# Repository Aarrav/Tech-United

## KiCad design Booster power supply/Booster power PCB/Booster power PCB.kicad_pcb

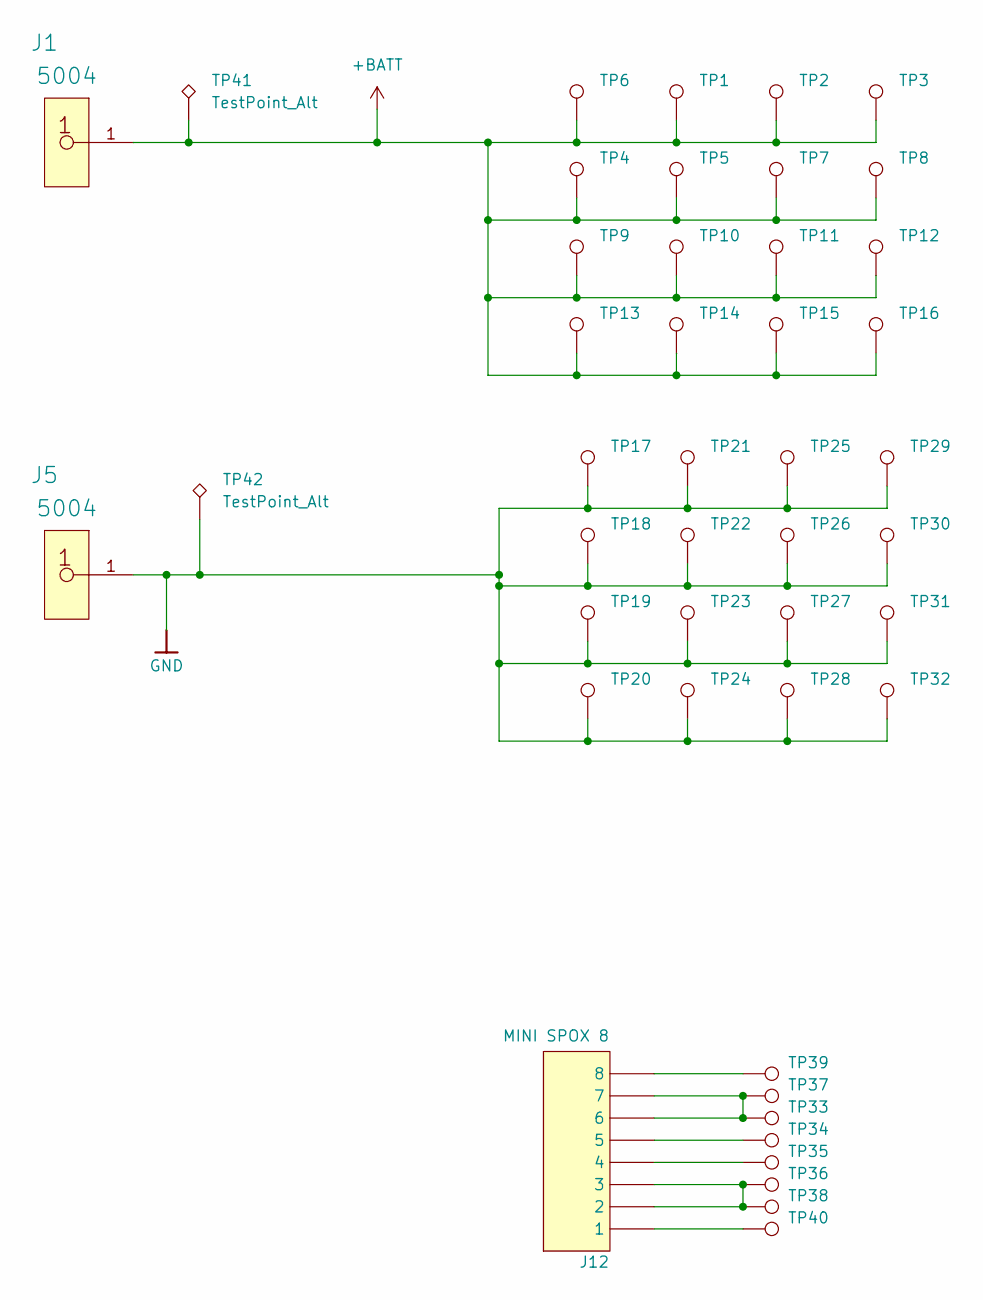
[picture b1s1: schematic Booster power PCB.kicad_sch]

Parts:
J1, J5: 5004; FP-5004-MFG; Manufacturer Part Number 5004; Digikey Description PC TEST POINT MINIATURE YELLOW
J12: MINI SPOX 8; MINI_SPOX_1X8_S; MANUFACTURER PART NUMBER 22-03-5085; JLCPCB PART # C588974
TP1, TP2: TestPoint; TestPoint_THTPad_2.0x2.0mm_Drill1.0mm
TP3, TP4, TP5, TP6, TP7, TP8, TP9, TP10, TP11, TP12, TP13, TP14, TP15, TP16, TP17, TP18, TP19, TP20, TP21, TP22, TP23, TP24, TP25, TP26, TP27, TP28, TP29, TP30, TP31, TP32, TP33, TP34, TP35, TP36, TP37, TP38, TP39, TP40: TestPoint; TestPoint_THTPad_2.0x2.0mm_Drill1.15mm
TP41, TP42: TestPoint_Alt; TestPoint_Plated_Hole_D3.0mm

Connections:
+BATT: J1.1, TP1.1, TP2.1, TP3.1, TP4.1, TP5.1, TP6.1, TP7.1, TP8.1, TP9.1, TP10.1, TP11.1, TP12.1, TP13.1, TP14.1, TP15.1, TP16.1, TP41.1
GND: J5.1, TP17.1, TP18.1, TP19.1, TP20.1, TP21.1, TP22.1, TP23.1, TP24.1, TP25.1, TP26.1, TP27.1, TP28.1, TP29.1, TP30.1, TP31.1, TP32.1, TP42.1
unnamed: J12.1, TP40.1
unnamed: J12.2, J12.3, TP36.1, TP38.1
unnamed: J12.4, TP35.1
unnamed: J12.5, TP34.1
unnamed: J12.6, J12.7, TP33.1, TP37.1
unnamed: J12.8, TP39.1

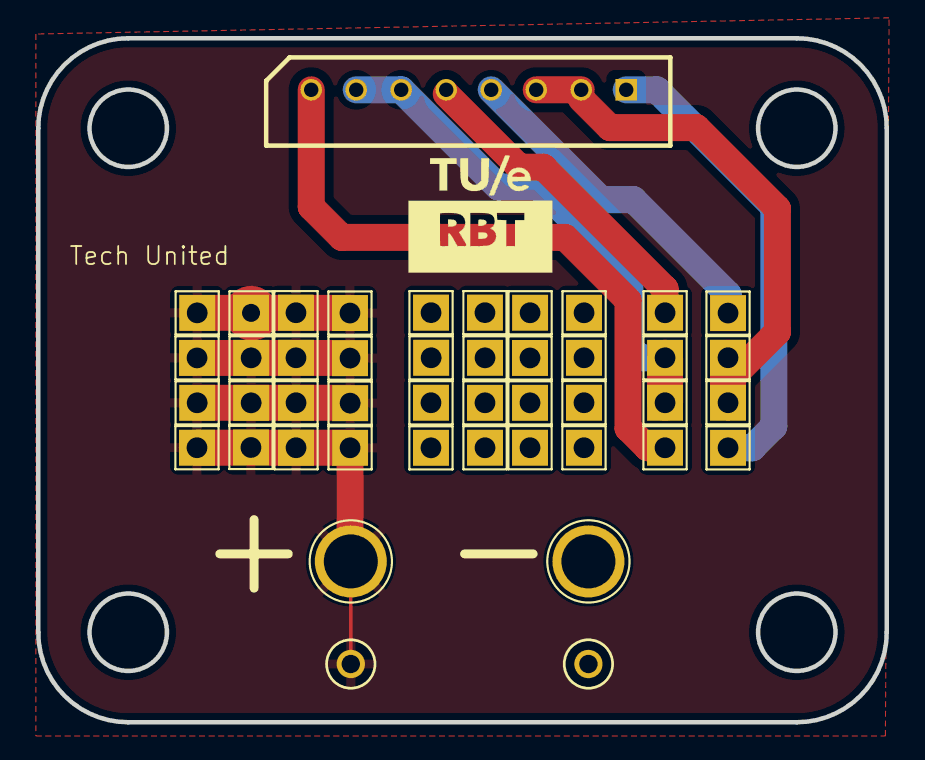
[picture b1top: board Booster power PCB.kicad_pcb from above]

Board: 2 copper layers, 47.1 x 38.0 mm, 45 parts (0 on the bottom side), 8 nets.

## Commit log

2026-01-17 Tech United
2026-01-17 slow reading working
2026-03-25 merged files
2026-04-04 Seeed Studio code
2026-04-04 Changed to robot's IP
2026-05-27 changed to robot's ip 10.0.0.20
2026-05-30 Added booster receiver code
2026-06-02 CAD files
2026-06-11 double sensor udp port
2026-06-11 voltage logger calibrated
2026-06-13 Wireless working
